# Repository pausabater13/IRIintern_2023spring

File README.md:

# IRIintern_2023spring
IRI INTERNSHIP
# Thrust Controller :leaves:

> Hardware and firmware of the HiDRo thrust controller board.

This board was designed in order to drive an UAM by thrust control.

The repository is made as follow:

- **documentation** folder contains what explain the differente part of the project (component list, how to ...),
- **firmware** folder contains the code to flash the board,
- **hardware** folder contains the Kicad CAD project to manufacture the board.

### More Information

[HiDRo](https://github.com/hidro-iri)

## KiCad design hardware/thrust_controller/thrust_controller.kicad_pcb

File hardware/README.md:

# Thurst Controller Hardware :notebook:

> Hardware files related to the HiDRo thrust controller board.

The hardware CAD files of the board have been created using Kicad.

Inside the **thrust_controller** folder you can find :

- the electrical schematic (*thrust_controller.kicad_sch*)
- the pcb design (*thrust_controller.kicad_pcb*)
- the fabrication files (in **fabrication_outputs**)

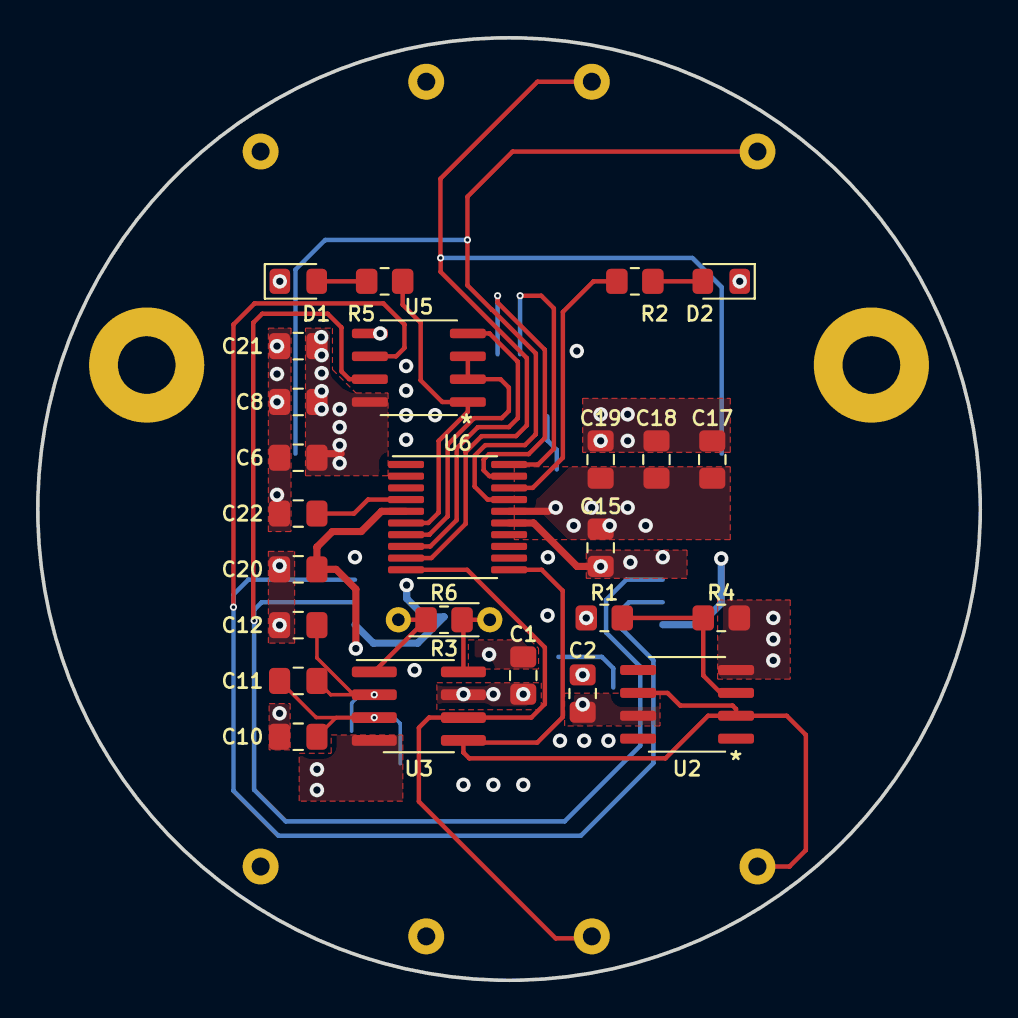
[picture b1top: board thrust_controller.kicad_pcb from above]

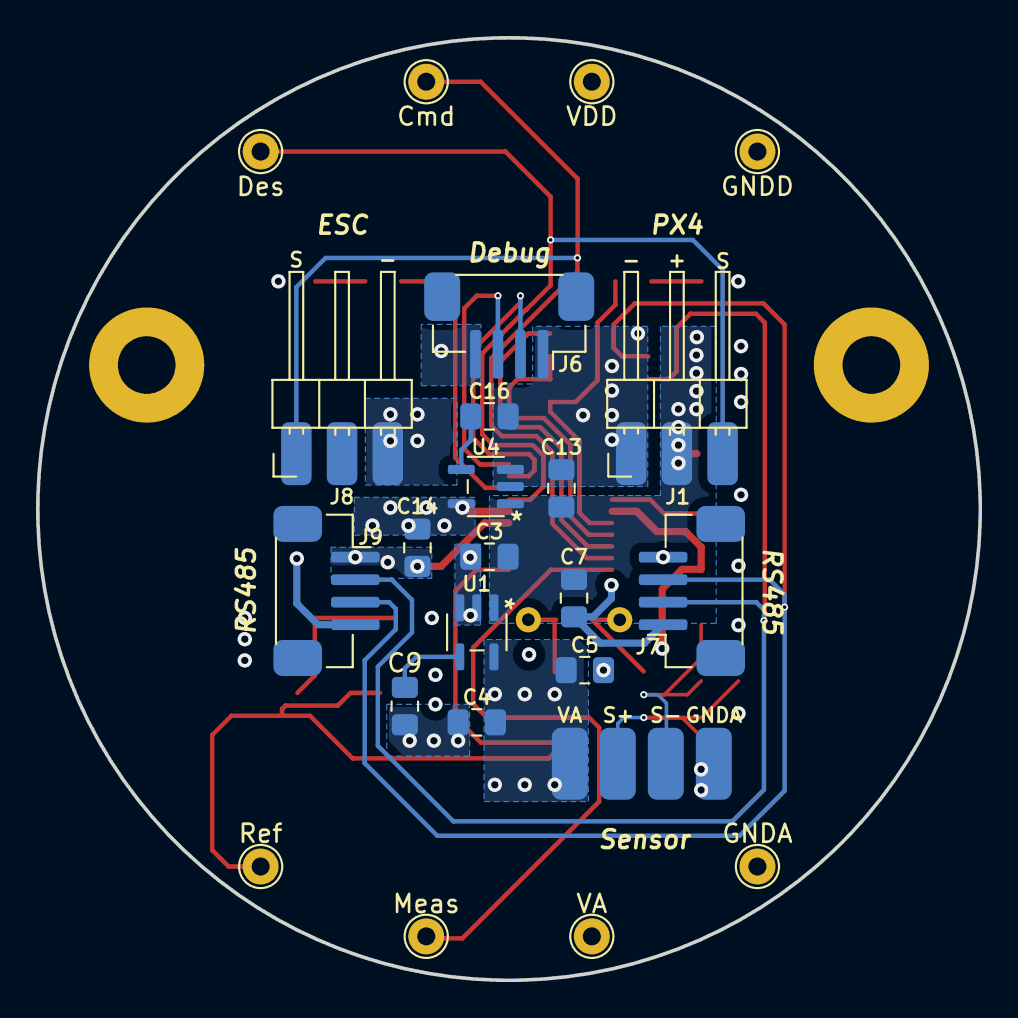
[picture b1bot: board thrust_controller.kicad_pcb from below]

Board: 4 copper layers, 52.4 x 52.4 mm, 55 parts (27 on the bottom side), 26 nets.

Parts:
C1, C2, C3, C9, C10, C11, C12, C13, C16, C17, C18, C19, C20, C21, C22: 0.1 μF; C_0805_2012Metric_Pad1.18x1.45mm_HandSolder
C4, C14: 1 μF; C_0805_2012Metric_Pad1.18x1.45mm_HandSolder
C5: 10 μF Tantalum; C_0805_2012Metric_Pad1.18x1.45mm_HandSolder
C6, C7, C8, C15: 10 μF; C_0805_2012Metric_Pad1.18x1.45mm_HandSolder
D1: BLUE LED; LED_0805_2012Metric_Pad1.15x1.40mm_HandSolder
D2: YELLOW LED; LED_0805_2012Metric_Pad1.15x1.40mm_HandSolder
H1, H2: MountingHole; MountingHole_3.2mm_M3_Pad
J1: px4_con; PinHeader_1x03_P2.54mm_Horizontal
J2: VS; SolderWirePad_1x01_SMD_1x2mm
J3: S+; SolderWirePad_1x01_SMD_1x2mm
J4: S-; SolderWirePad_1x01_SMD_1x2mm
J5: GND; SolderWirePad_1x01_SMD_1x2mm
J6: debug_con; JST_GH_SM04B-GHS-TB_1x04-1MP_P1.25mm_Horizontal
J7, J9: rs485_con; JST_GH_SM04B-GHS-TB_1x04-1MP_P1.25mm_Horizontal
J8: esc_con; PinHeader_1x03_P2.54mm_Horizontal
R1, R4: R; R_0805_2012Metric_Pad1.20x1.40mm_HandSolder
R2: 260 Ω; R_0805_2012Metric_Pad1.20x1.40mm_HandSolder
R3: Rg; R_0805_2012Metric_Pad1.20x1.40mm_HandSolder
R5: 440 Ω; R_0805_2012Metric_Pad1.20x1.40mm_HandSolder
R6: Test; R_Axial_DIN0204_L3.6mm_D1.6mm_P5.08mm_Horizontal
TP1, TP2, TP3, TP4, TP5, TP6, TP7, TP8: TestPoint; TestPoint_THTPad_D2.0mm_Drill1.0mm
U1, U4: TPS79133DBVT
U2: OPA317ID
U3: AD620; SOIC-8_3.9x4.9mm_P1.27mm
U5: MAX485E; MAX1487ESA&plus_
U6: STM32L011F4Px; TSSOP-20_4.4x6.5mm_P0.65mm

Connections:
+3.3V: C14.1, C15.1, C17.1, C18.1, C19.1, J6.4, J7.4, J9.4, TP5.1, U4.5 (OUT), U6.16 (VDD)
+3.3VA: C1.1, C2.1, C4.1, C5.1, C10.1, C20.1, J2.1, R1.1, TP1.1, U1.5 (OUT), U2.7 (V+), U3.7 (Vs+), U6.5 (VDDA)
+5V: C3.1, C6.1, C7.1, C8.1, C13.1, C21.1, J1.2, U1.1 (IN), U4.1 (IN), U5.8 (VCC)
A: J7.3, J9.3, U5.6 (A)
B: J7.2, J9.2, U5.7 (B)
Cmd: J8.1, TP7.1, U6.9 (PA3)
Des: J1.3, TP2.1, U6.17 (PA9)
GNDA: C1.2, C2.2, C3.2, C4.2, C5.2, C6.2, C7.2, C8.2, C9.2, C12.2, C13.2, C14.2, C15.2, C16.2, C17.2, C18.2, C19.2, C20.2, C21.2, C22.2, D1.1 (K), D2.1 (K), J1.1, J5.1, J6.1, J7.1, J8.3, J9.1, R4.2, TP6.1, TP8.1, U1.2 (GND), U1.3 (*EN), U2.4 (V-), U3.4 (Vs-), U4.2 (GND), U4.3 (*EN), U5.5 (GND), U6.15 (VSS)
Meas: TP3.1, U3.6, U6.10 (PA4)
unnamed: C9.1, U1.4 (BP)
unnamed: C16.1, U4.4 (BP)
unnamed: C22.1, U6.4 (NRST)
unnamed: D1.2 (A), R5.1
unnamed: D2.2 (A), R2.2
unnamed: R1.2, R4.1, U2.3 (+)
unnamed: R2.1, U6.18 (PA10)
unnamed: R3.1, R6.1, U3.1 (Rg)
unnamed: R3.2, R6.2, U3.8 (Rg)
unnamed: U5.2 (~RE), U5.3 (DE), U6.7 (PA1)
Ref: TP4.1, U2.2 (-), U2.6, U3.5 (Ref), U6.11 (PA5)
S+: C10.2, C11.1, J3.1, U3.3 (+)
S-: C11.2, C12.1, J4.1, U3.2 (-)
SWCLK: J6.3, U6.20 (PA14)
SWDIO: J6.2, U6.19 (PA13)
USART2_RX: R5.2, U5.1 (RO), U6.6 (PA0)
USART2_TX: U5.4 (DI), U6.8 (PA2)

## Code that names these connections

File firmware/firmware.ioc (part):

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Mcu.Name=STM32L011F(3-4)Px
Mcu.Package=TSSOP20
Mcu.UserName=STM32L011F4Px
PA0-CK_IN.Mode=Asynchronous
PA0-CK_IN.Signal=USART2_RX
PA10.GPIOParameters=GPIO_Label
PA10.GPIO_Label=STATUS_LED
PA10.Signal=GPIO_Input
PA13.Mode=Serial_Wire
PA13.Signal=SYS_SWDIO
PA14.Mode=Serial_Wire
PA14.Signal=SYS_SWCLK
PA2.Mode=Asynchronous
PA2.Signal=USART2_TX
PA3.GPIOParameters=GPIO_Speed,GPIO_Label
PA3.GPIO_Label=CMD_PWM_OUT
PA3.GPIO_Speed=GPIO_SPEED_FREQ_VERY_HIGH
PA3.Signal=S_TIM2_CH4
PA4.GPIOParameters=GPIO_Label
PA4.GPIO_Label=MEAS_ANL_IN
PA4.Signal=SharedAnalog_PA4
PA5.GPIOParameters=GPIO_Label
PA5.GPIO_Label=REF_ANL_IN
PA5.Signal=SharedAnalog_PA5
PA9.GPIOParameters=GPIO_Speed,GPIO_Label
PA9.GPIO_Label=DES_PWM_IN
PA9.GPIO_Speed=GPIO_SPEED_FREQ_VERY_HIGH
PA9.Signal=S_TIM21_CH2
RCC.HSE_VALUE=8000000
RCC.SYSCLKFreq_VALUE=32000000
RCC.SYSCLKSource=RCC_SYSCLKSOURCE_PLLCLK
board=custom

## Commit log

2023-03-31 Create hola
2023-05-12 Create Thrust_control.c
    STM32 CubeIDE main.c for thrust control with ADC, TIM2 for PWM generation and TIM21 with channels 1 and 2 for pulse length input reading.
2023-05-12 feat: Add last internship updates

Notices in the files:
parts and their libraries:
Copyright 2021 Accelerated Designs. All rights reserved.
